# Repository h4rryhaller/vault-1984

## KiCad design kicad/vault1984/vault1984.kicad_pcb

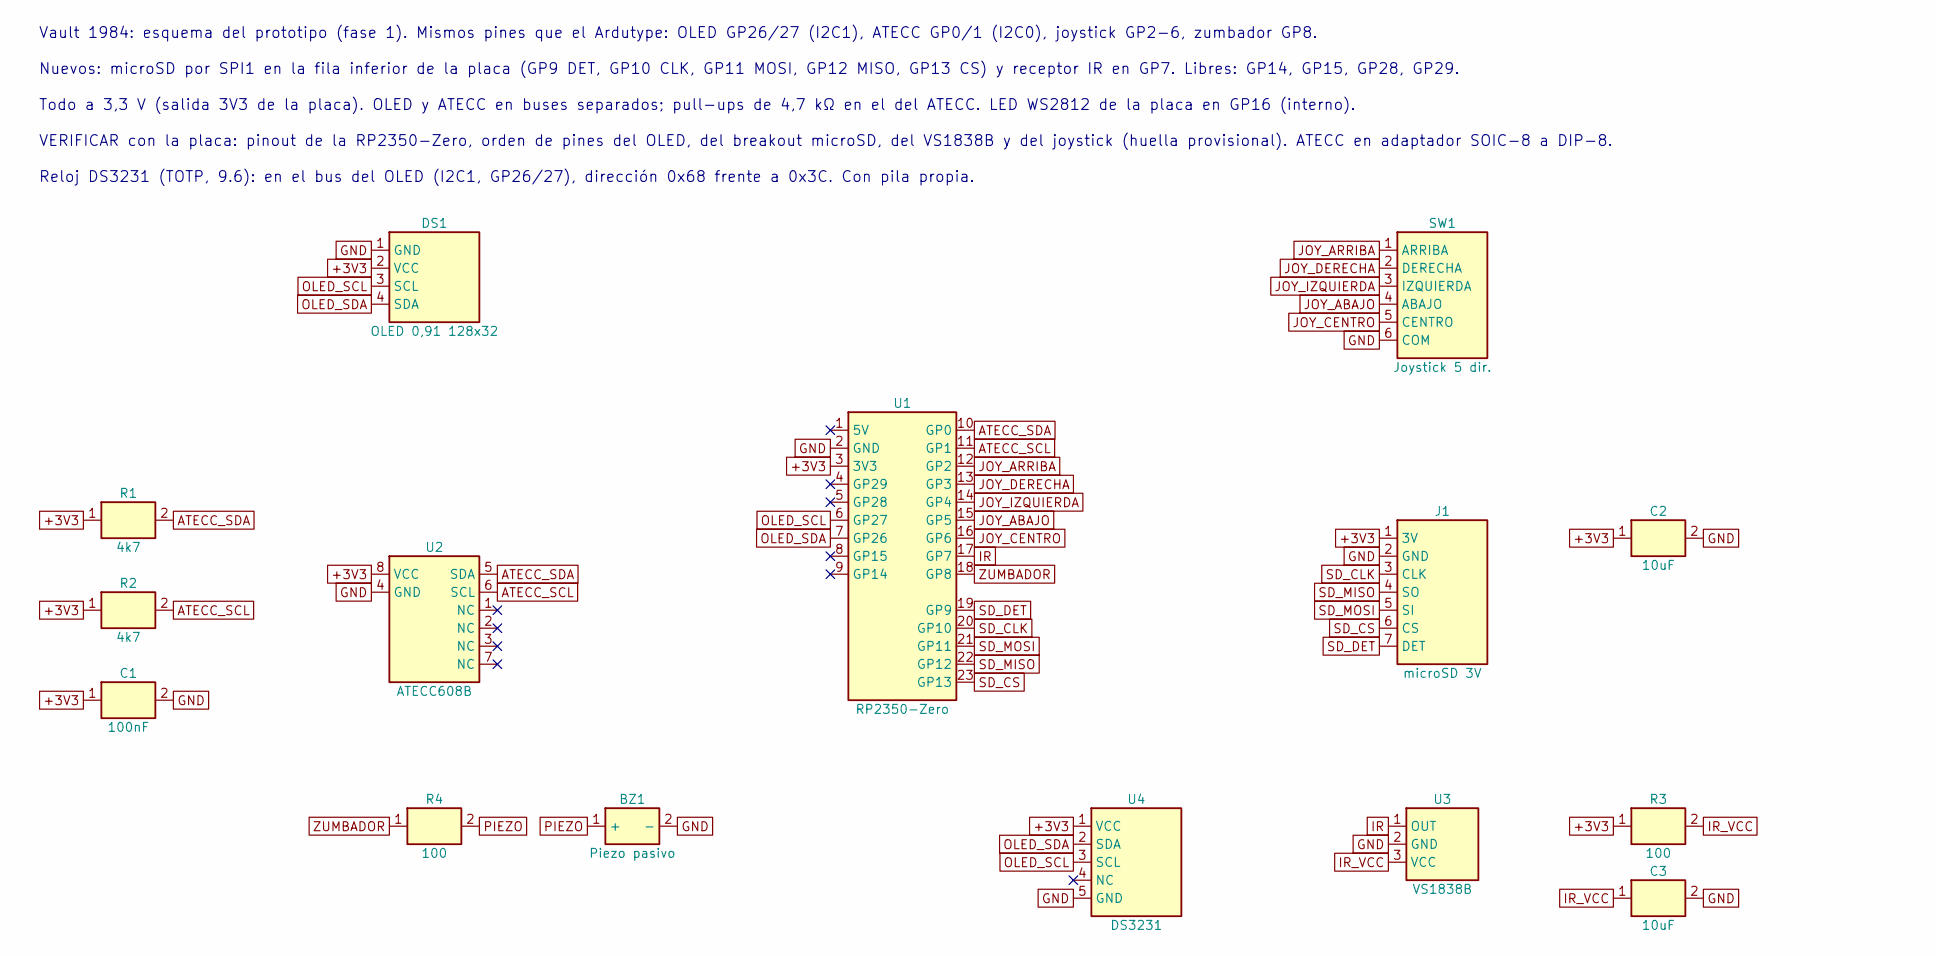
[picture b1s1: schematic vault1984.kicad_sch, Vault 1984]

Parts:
BZ1: Piezo pasivo; Buzzer_12x9.5RM7.6
C1: 100nF; C_Disc_D5.0mm_W2.5mm_P2.50mm
C2, C3: 10uF; CP_Radial_D5.0mm_P2.50mm
DS1: OLED 0,91 128x32; OLED_091_128x32
J1: microSD 3V; microSD_breakout_3V
R1, R2: 4k7; R_Axial_DIN0207_L6.3mm_D2.5mm_P7.62mm_Horizontal
R3, R4: 100; R_Axial_DIN0207_L6.3mm_D2.5mm_P7.62mm_Horizontal
SW1: Joystick 5 dir.; Joystick_10x10
U1: RP2350-Zero; RP2350_Zero
U2: ATECC608B; DIP-8_W7.62mm
U3: VS1838B
U4: DS3231; DS3231_mini_RPi

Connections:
+3V3: C1.1, C2.1, DS1.2 (VCC), J1.1 (3V), R1.1, R2.1, R3.1, U1.3 (3V3), U2.8 (VCC), U4.1 (VCC)
ATECC_SCL: R2.2, U1.11 (GP1), U2.6 (SCL)
ATECC_SDA: R1.2, U1.10 (GP0), U2.5 (SDA)
GND: BZ1.2 (-), C1.2, C2.2, C3.2, DS1.1 (GND), J1.2 (GND), SW1.6 (COM), U1.2 (GND), U2.4 (GND), U3.2 (GND), U4.5 (GND)
IR: U1.17 (GP7), U3.1 (OUT)
IR_VCC: C3.1, R3.2, U3.3 (VCC)
JOY_ABAJO: SW1.4 (ABAJO), U1.15 (GP5)
JOY_ARRIBA: SW1.1 (ARRIBA), U1.12 (GP2)
JOY_CENTRO: SW1.5 (CENTRO), U1.16 (GP6)
JOY_DERECHA: SW1.2 (DERECHA), U1.13 (GP3)
JOY_IZQUIERDA: SW1.3 (IZQUIERDA), U1.14 (GP4)
OLED_SCL: DS1.3 (SCL), U1.6 (GP27), U4.3 (SCL)
OLED_SDA: DS1.4 (SDA), U1.7 (GP26), U4.2 (SDA)
PIEZO: BZ1.1 (+), R4.2
SD_CLK: J1.3 (CLK), U1.20 (GP10)
SD_CS: J1.6 (CS), U1.23 (GP13)
SD_DET: J1.7 (DET), U1.19 (GP9)
SD_MISO: J1.4 (SO), U1.22 (GP12)
SD_MOSI: J1.5 (SI), U1.21 (GP11)
ZUMBADOR: R4.1, U1.18 (GP8)

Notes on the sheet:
Vault 1984: esquema del prototipo (fase 1). Mismos pines que el Ardutype: OLED GP26/27 (I2C1), ATECC GP0/1 (I2C0), joystick GP2-6, zumbador GP8.
Nuevos: microSD por SPI1 en la fila inferior de la placa (GP9 DET, GP10 CLK, GP11 MOSI, GP12 MISO, GP13 CS) y receptor IR en GP7. Libres: GP14, GP15, GP28, GP29.
Todo a 3,3 V (salida 3V3 de la placa). OLED y ATECC en buses separados; pull-ups de 4,7 kΩ en el del ATECC. LED WS2812 de la placa en GP16 (interno).
VERIFICAR con la placa: pinout de la RP2350-Zero, orden de pines del OLED, del breakout microSD, del VS1838B y del joystick (huella provisional). ATECC en adaptador SOIC-8 a DIP-8.
Reloj DS3231 (TOTP, 9.6): en el bus del OLED (I2C1, GP26/27), dirección 0x68 frente a 0x3C. Con pila propia.

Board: 2 copper layers, 15 parts (0 on the bottom side), 20 nets, no tracks yet.
